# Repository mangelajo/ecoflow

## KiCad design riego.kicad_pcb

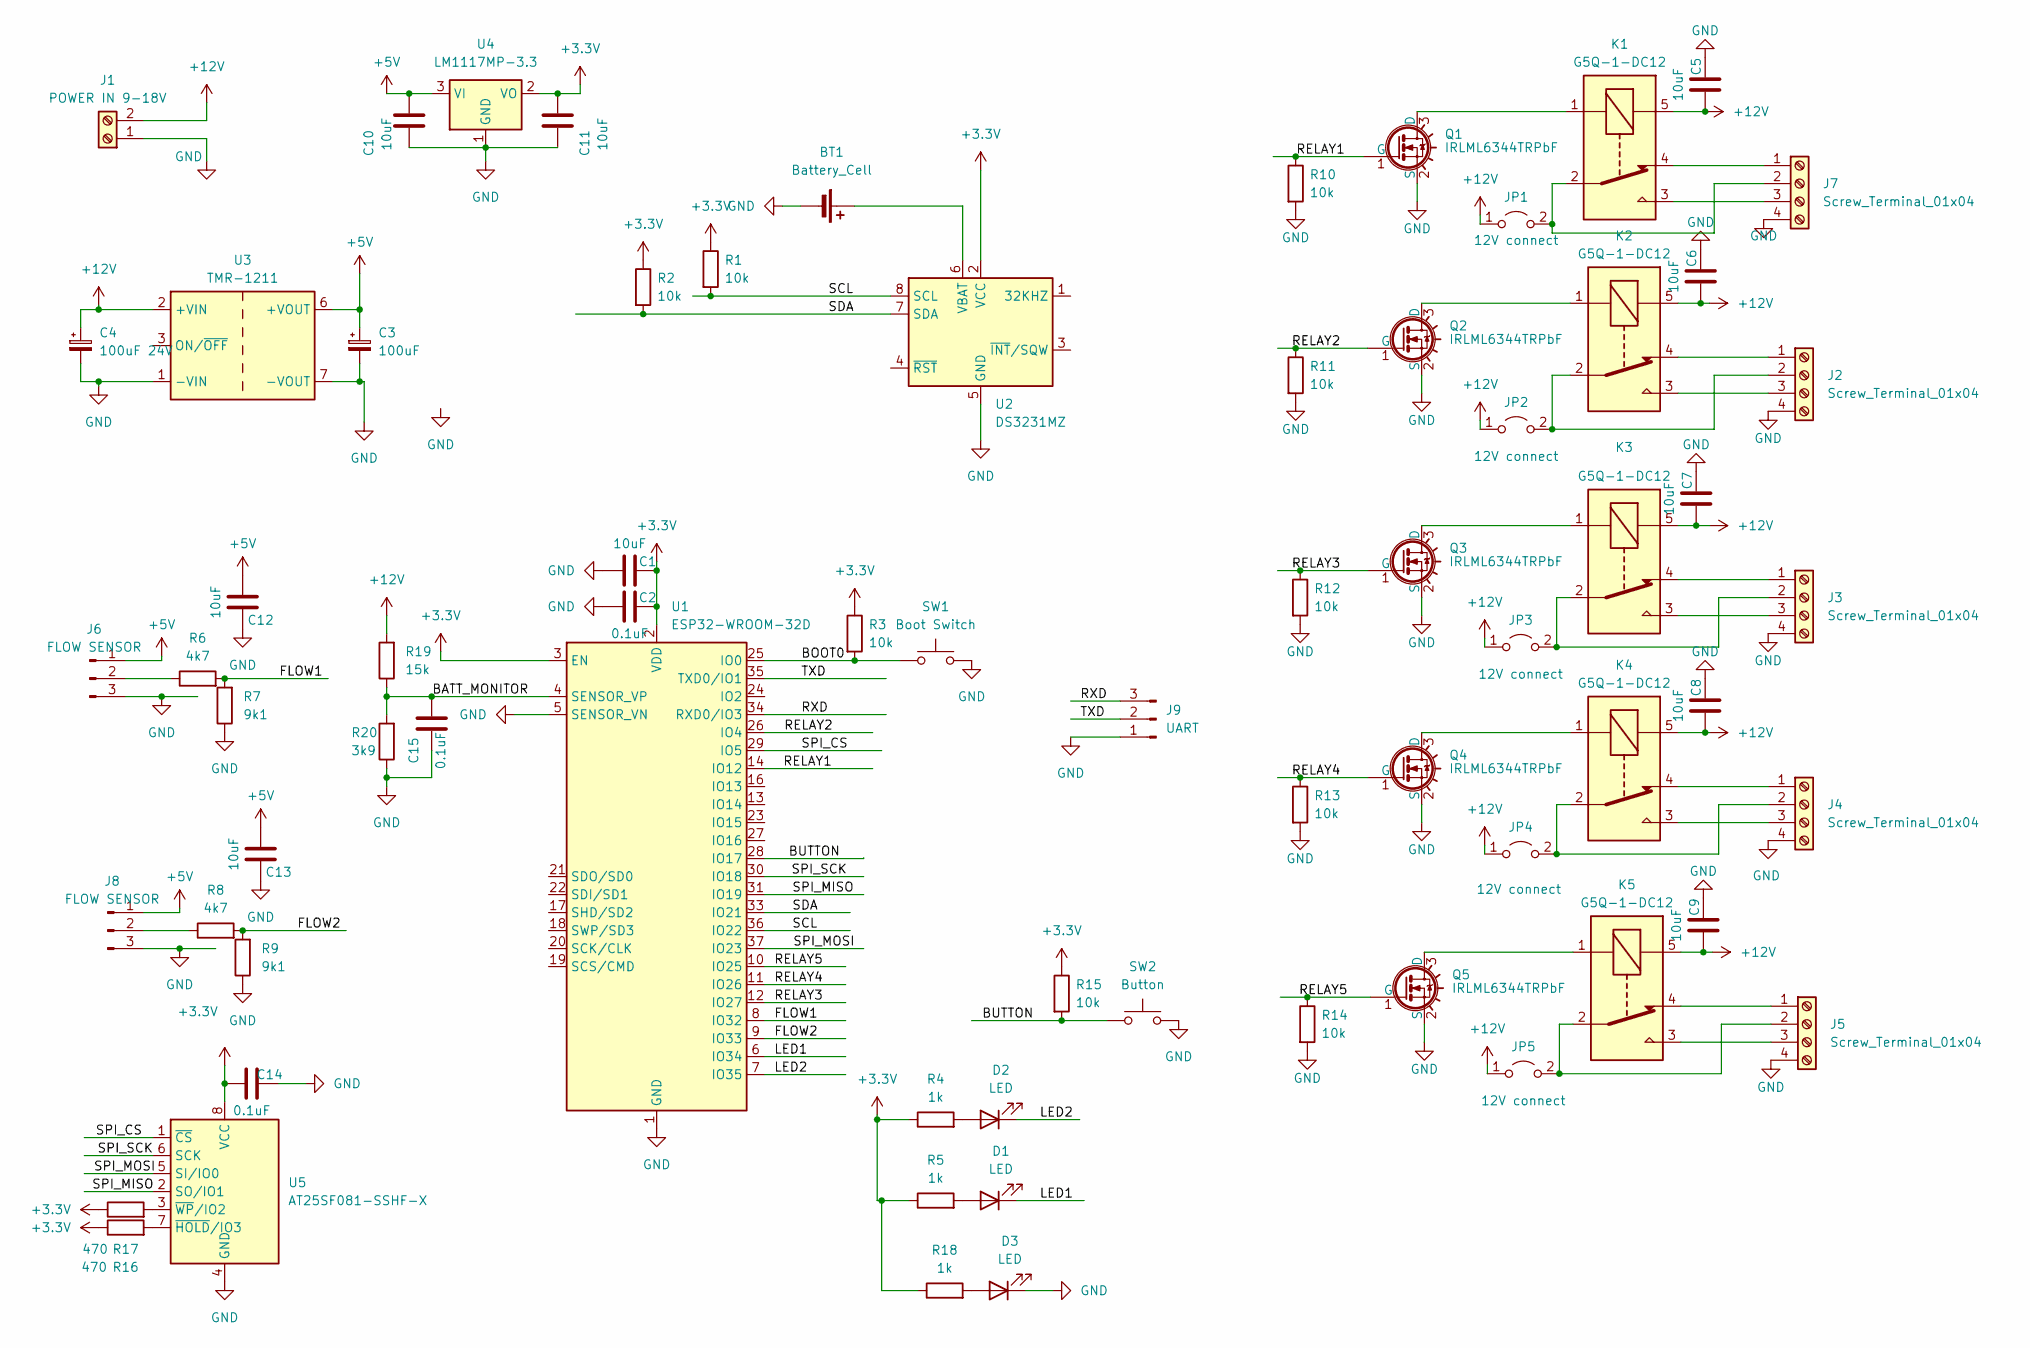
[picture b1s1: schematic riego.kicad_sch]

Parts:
BT1: Battery_Cell; BatteryHolder_Keystone_103_1x20mm
C1, C5, C6, C7, C8, C9, C10, C11, C12, C13: 10uF; C_0603_1608Metric
C2, C14, C15: 0.1uF; C_0603_1608Metric
C3: 100uF; CP_Radial_D8.0mm_P5.00mm
C4: 100uF 24V; CP_Radial_D8.0mm_P5.00mm
D1, D2, D3: LED; LED_0805_2012Metric
J1: POWER IN 9-18V; TerminalBlock_bornier-2_P5.08mm
J2, J3, J4, J5, J7: Screw_Terminal_01x04; TerminalBlock_bornier-4_P5.08mm
J6, J8: FLOW SENSOR; TerminalBlock_bornier-3_P5.08mm
J9: UART; PinHeader_1x03_P2.54mm_Vertical
JP1, JP2, JP3, JP4, JP5: 12V connect; PinHeader_1x02_P2.54mm_Vertical
K1, K2, K3, K4, K5: G5Q-1-DC12; Relay_SPDT_Omron-G5Q-1
Q1, Q2, Q3, Q4, Q5: IRLML6344TRPbF; SOT-23
R1, R2, R3, R10, R11, R12, R13, R14, R15: 10k; R_0603_1608Metric
R4, R5, R18: 1k; R_0603_1608Metric
R6, R8: 4k7; R_0603_1608Metric
R7, R9: 9k1; R_0603_1608Metric
R16, R17: 470; R_0603_1608Metric
R19: 15k; R_0603_1608Metric
R20: 3k9; R_0603_1608Metric
SW1: Boot Switch; SW_PUSH_6mm_H4.3mm
SW2: Button; SW_PUSH_6mm_H4.3mm
U1: ESP32-WROOM-32D
U2: DS3231MZ; SOIC-8_3.9x4.9mm_P1.27mm
U3: TMR-1211; Converter_DCDC_TRACO_TMR-xxxx_THT
U4: LM1117MP-3.3; SOT-223-3_TabPin2
U5: AT25SF081-SSHF-X; SOIC-8_3.9x4.9mm_P1.27mm

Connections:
+3.3V: C1.2, C2.2, C11.1, C14.1, R1.1, R2.1, R3.1, R4.1, R5.1, R15.1, R16.1, R17.1, R18.1, U1.2 (VDD), U1.3 (EN), U2.2 (VCC), U4.2 (VO), U5.8 (VCC)
+5V: C3.1, C10.1, C12.2, C13.2, J6.1, J8.1, U3.6 (+VOUT), U4.3 (VI)
+12V: C4.1, C5.1, C6.1, C7.1, C8.1, C9.1, J1.2, JP1.1 (A), JP2.1 (A), JP3.1 (A), JP4.1 (A), JP5.1 (A), K1.5, K2.5, K3.5, K4.5, K5.5, R19.2, U3.2 (+VIN)
/BATT_MONITOR: C15.2, R19.1, R20.2, U1.4 (SENSOR_VP)
/BOOT0: R3.2, SW1.1, U1.25 (IO0)
/BUTTON: R15.2, SW2.1, U1.28 (IO17)
/FLOW1: R6.2, R7.2, U1.8 (IO32)
/FLOW2: R8.2, R9.2, U1.9 (IO33)
/LED1: D1.1 (K), U1.6 (IO34)
/LED2: D2.1 (K), U1.7 (IO35)
/RELAY1: Q1.1 (G), R10.1, U1.14 (IO12)
/RELAY2: Q2.1 (G), R11.1, U1.26 (IO4)
/RELAY3: Q3.1 (G), R12.1, U1.12 (IO27)
/RELAY4: Q4.1 (G), R13.1, U1.11 (IO26)
/RELAY5: Q5.1 (G), R14.1, U1.10 (IO25)
/RXD: J9.3, U1.34 (RXD0/IO3)
/SCL: R1.2, U1.36 (IO22), U2.8 (SCL)
/SDA: R2.2, U1.33 (IO21), U2.7 (SDA)
/SPI_CS: U1.29 (IO5), U5.1 (~CS)
/SPI_MISO: U1.31 (IO19), U5.2 (SO/IO1)
/SPI_MOSI: U1.37 (IO23), U5.5 (SI/IO0)
/SPI_SCK: U1.30 (IO18), U5.6 (SCK)
/TXD: J9.2, U1.35 (TXD0/IO1)
GND: BT1.2 (-), C1.1, C2.1, C3.2, C4.2, C5.2, C6.2, C7.2, C8.2, C9.2, C10.2, C11.2, C12.1, C13.1, C14.2, C15.1, D3.1 (K), J1.1, J2.4, J3.4, J4.4, J5.4, J6.3, J7.4, J8.3, J9.1, Q1.2 (S), Q2.2 (S), Q3.2 (S), Q4.2 (S), Q5.2 (S), R7.1, R9.1, R10.2, R11.2, R12.2, R13.2, R14.2, R20.1, SW1.2, SW2.2, U1.1 (GND), U1.5 (SENSOR_VN), U1.15 (GND), U1.38 (GND), U1.39 (GND), U2.5 (GND), U3.1 (-VIN), U3.7 (-VOUT), U4.1 (GND), U5.4 (GND)
unnamed: BT1.1 (+), U2.6 (VBAT)
unnamed: D1.2 (A), R5.2
unnamed: D2.2 (A), R4.2
unnamed: D3.2 (A), R18.2
unnamed: J2.1, K2.4
unnamed: J2.2, JP2.2 (B), K2.2
unnamed: J2.3, K2.3
unnamed: J3.1, K3.4
unnamed: J3.2, JP3.2 (B), K3.2
unnamed: J3.3, K3.3
unnamed: J4.1, K4.4
unnamed: J4.2, JP4.2 (B), K4.2
unnamed: J4.3, K4.3
unnamed: J5.1, K5.4
unnamed: J5.2, JP5.2 (B), K5.2
unnamed: J5.3, K5.3
unnamed: J6.2, R6.1
unnamed: J7.1, K1.4
unnamed: J7.2, JP1.2 (B), K1.2
unnamed: J7.3, K1.3
unnamed: J8.2, R8.1
unnamed: K1.1, Q1.3 (D)
unnamed: K2.1, Q2.3 (D)
unnamed: K3.1, Q3.3 (D)
unnamed: K4.1, Q4.3 (D)
unnamed: K5.1, Q5.3 (D)
unnamed: R16.2, U5.7 (~HOLD/IO3)
unnamed: R17.2, U5.3 (~WP/IO2)

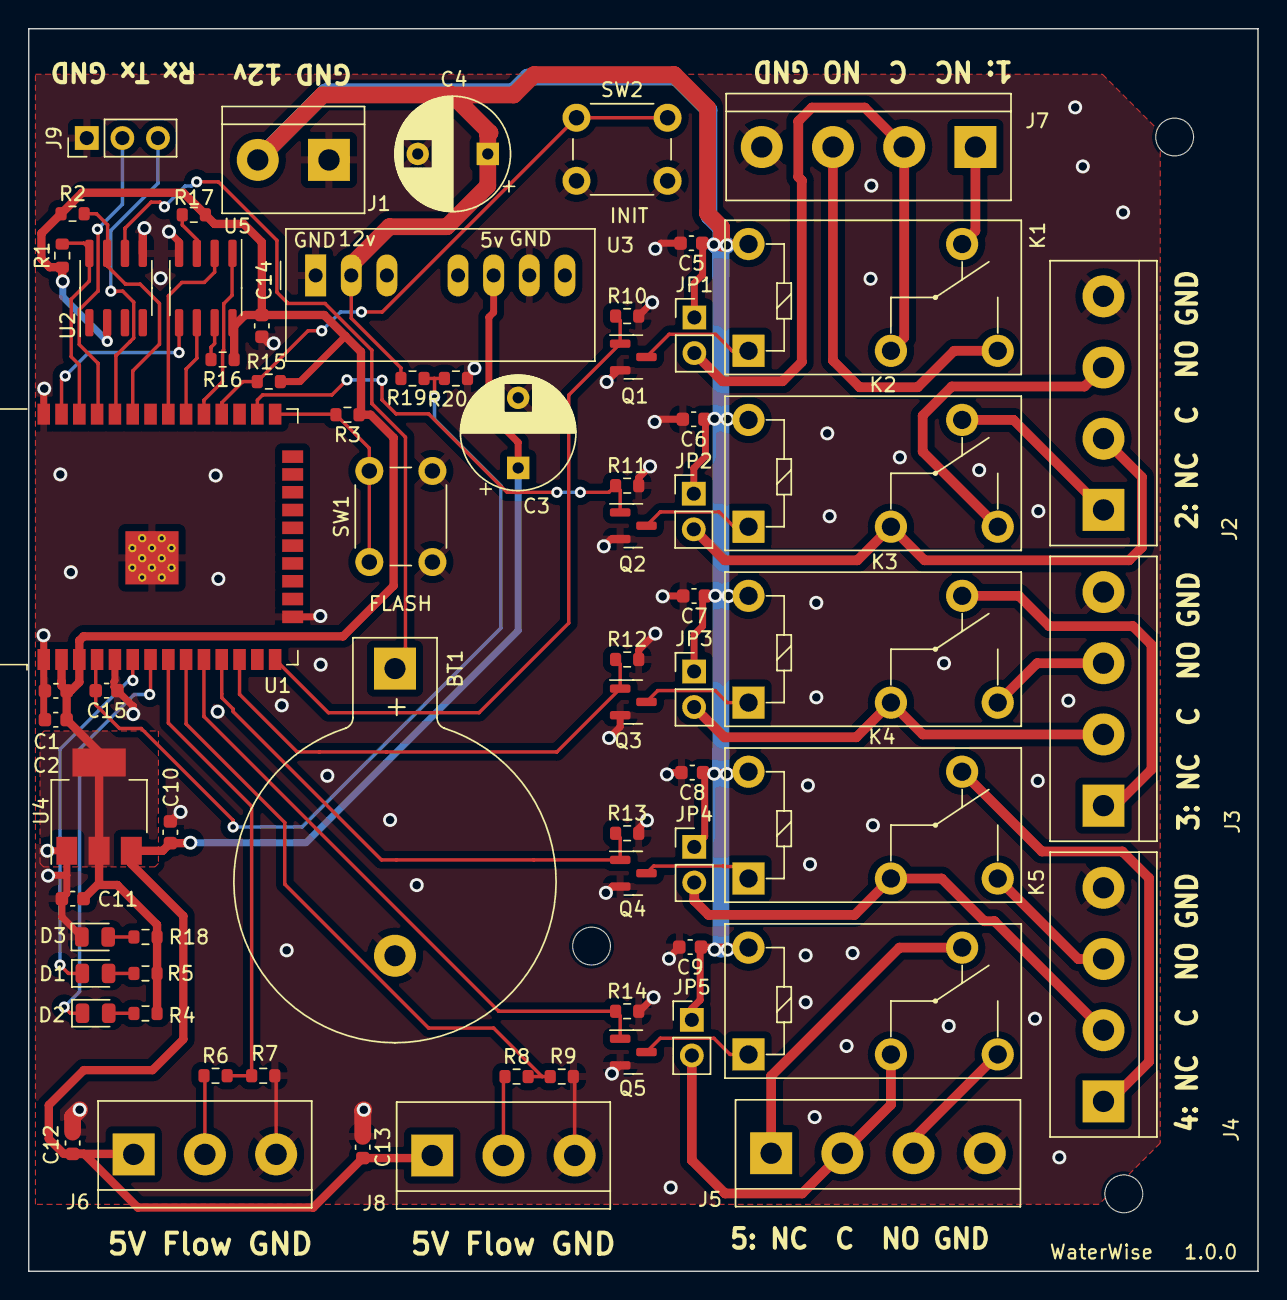
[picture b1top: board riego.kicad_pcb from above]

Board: 2 copper layers, 87.7 x 88.7 mm, 70 parts (0 on the bottom side), 52 nets.

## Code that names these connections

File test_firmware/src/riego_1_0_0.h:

#ifndef __HARDWARE_PINS
#define __HARDWARE_PINS

#define RELAY1 12
#define RELAY2 4
#define RELAY3 27
#define RELAY4 26
#define RELAY5 25

//#define LED1 34
//#define LED2 35

#define LED1 13 
#define LED2 14

#define I2C_SDA 21
#define I2C_SCL 22

#define SPI_CS   5
#define SPI_MOSI 23 
#define SPI_MISO 19
#define SPI_SCK  18

#define SENSOR1 32
#define SENSOR2 33

#define VIN_SENSOR 36
#endif

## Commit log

2023-09-04 add test firmware
2023-09-08 Test the RTC
